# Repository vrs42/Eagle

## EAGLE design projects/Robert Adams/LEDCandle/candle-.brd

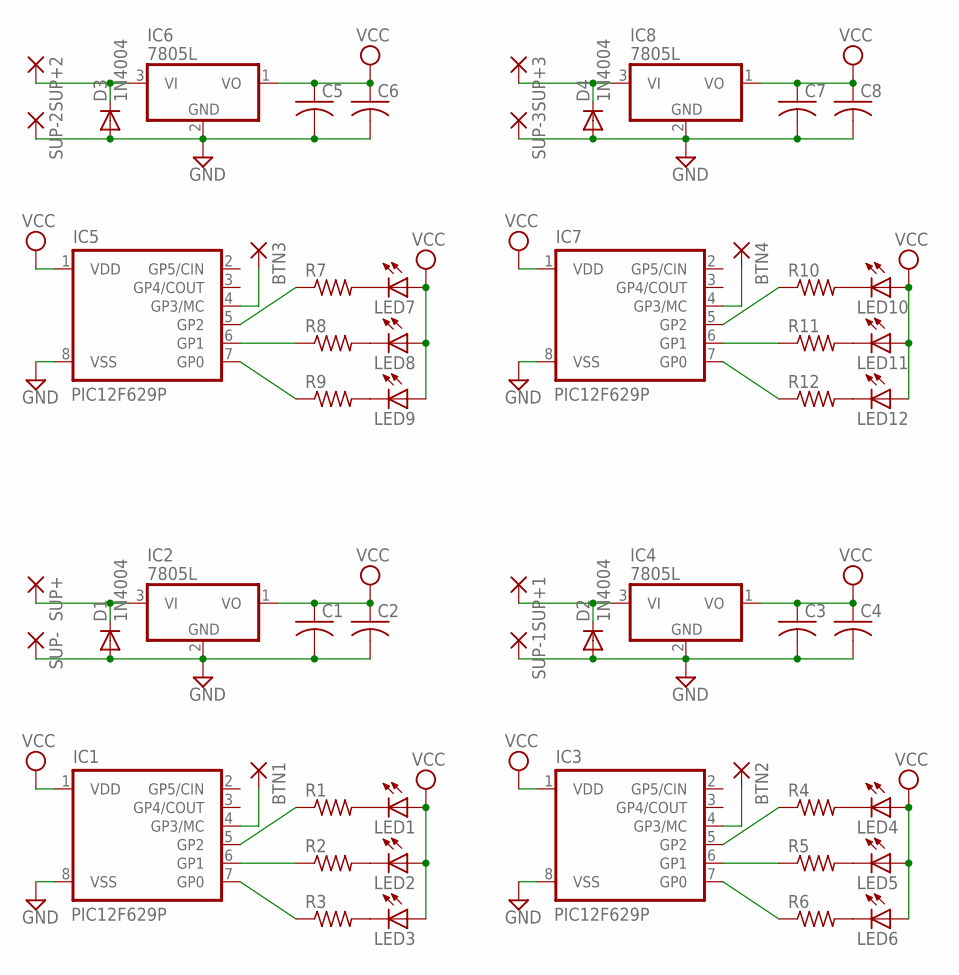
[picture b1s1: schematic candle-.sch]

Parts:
BTN1, BTN2, BTN3, BTN4: 1,6/0,8
C1, C2, C3, C4, C5, C6, C7, C8: C-US025-025X050; C025-025X050
D1, D2, D3, D4: 1N4004; DO41-10
IC1, IC3, IC5, IC7: PIC12F629P; DIL8
IC2, IC4, IC6, IC8: 7805L; TO92
LED1, LED2, LED3, LED4, LED5, LED6, LED7, LED8, LED9, LED10, LED11, LED12: LED5MM
R1, R2, R3, R4, R5, R6, R7, R8, R9, R10, R11, R12: R-US_0204/7; 0204/7
SUP+, SUP+1, SUP+2, SUP+3: 1,6/0,8
SUP-, SUP-1, SUP-2, SUP-3: 1,6/0,8

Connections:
GND: C1.2, C2.2, C3.2, C4.2, C5.2, C6.2, C7.2, C8.2, D1.A, D2.A, D3.A, D4.A, IC1.8 (VSS), IC2.2 (GND), IC3.8 (VSS), IC4.2 (GND), IC5.8 (VSS), IC6.2 (GND), IC7.8 (VSS), IC8.2 (GND), SUP-.1, SUP-1.1, SUP-2.1, SUP-3.1
unnamed: IC3.7 (GP0), R6.1
unnamed: BTN1.1, IC1.4 (GP3/MC)
unnamed: IC1.7 (GP0), R3.1
unnamed: IC1.6 (GP1), R2.1
unnamed: IC1.5 (GP2), R1.1
unnamed: LED1.K (C), R1.2
unnamed: LED2.K (C), R2.2
unnamed: LED3.K (C), R3.2
unnamed: IC3.6 (GP1), R5.1
unnamed: D1.C, IC2.3 (VI), SUP+.1
unnamed: IC3.5 (GP2), R4.1
unnamed: LED4.K (C), R4.2
unnamed: LED5.K (C), R5.2
unnamed: LED6.K (C), R6.2
unnamed: D2.C, IC4.3 (VI), SUP+1.1
unnamed: BTN2.1, IC3.4 (GP3/MC)
unnamed: IC5.7 (GP0), R9.1
unnamed: IC5.6 (GP1), R8.1
unnamed: IC5.5 (GP2), R7.1
unnamed: LED7.K (C), R7.2
unnamed: LED8.K (C), R8.2
unnamed: LED9.K (C), R9.2
unnamed: D3.C, IC6.3 (VI), SUP+2.1
unnamed: BTN3.1, IC5.4 (GP3/MC)
unnamed: IC7.7 (GP0), R12.1
unnamed: IC7.6 (GP1), R11.1
unnamed: IC7.5 (GP2), R10.1
unnamed: LED10.K (C), R10.2
unnamed: LED11.K (C), R11.2
unnamed: LED12.K (C), R12.2
unnamed: D4.C, IC8.3 (VI), SUP+3.1
unnamed: BTN4.1, IC7.4 (GP3/MC)
VCC: C1.1, C2.1, C3.1, C4.1, C5.1, C6.1, C7.1, C8.1, IC1.1 (VDD), IC2.1 (VO), IC3.1 (VDD), IC4.1 (VO), IC5.1 (VDD), IC6.1 (VO), IC7.1 (VDD), IC8.1 (VO), LED1.A, LED2.A, LED3.A, LED4.A, LED5.A, LED6.A, LED7.A, LED8.A, LED9.A, LED10.A, LED11.A, LED12.A

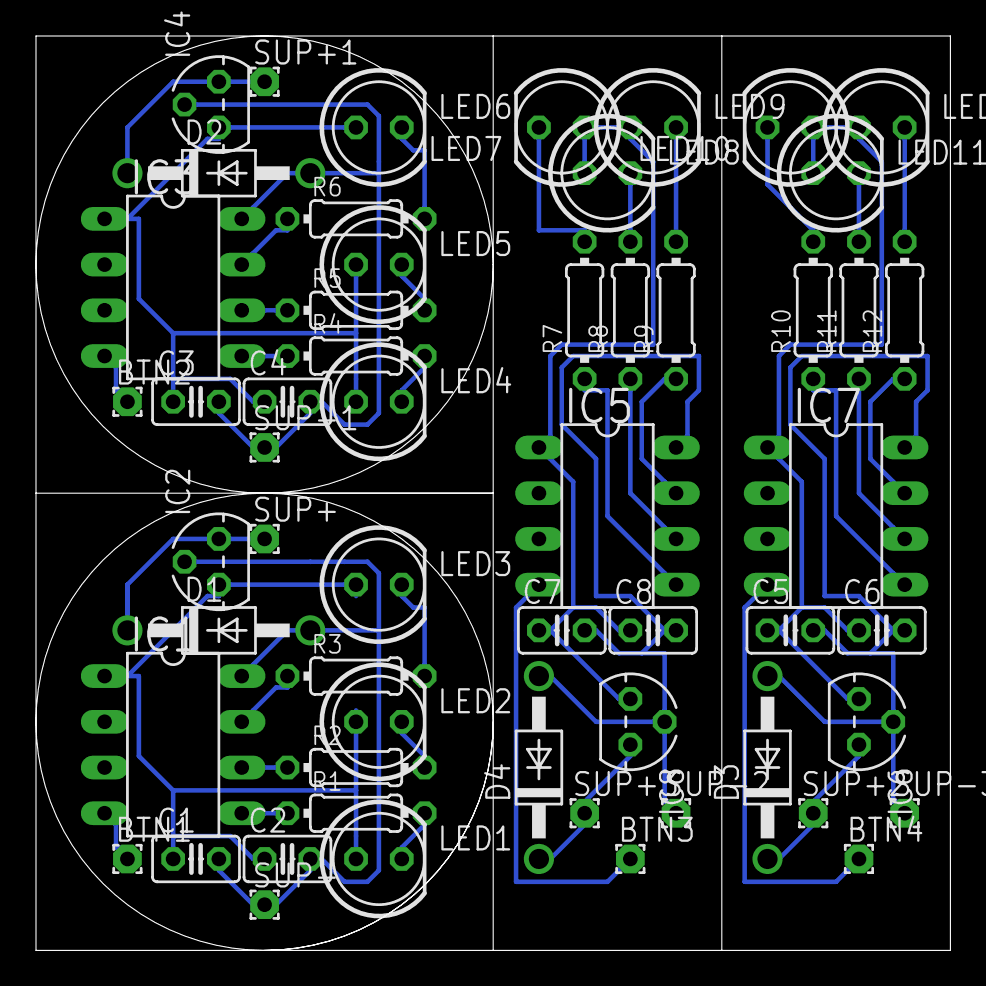
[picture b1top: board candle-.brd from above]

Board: 2 copper layers, 50.8 x 50.8 mm, 56 parts (0 on the bottom side), 34 nets.

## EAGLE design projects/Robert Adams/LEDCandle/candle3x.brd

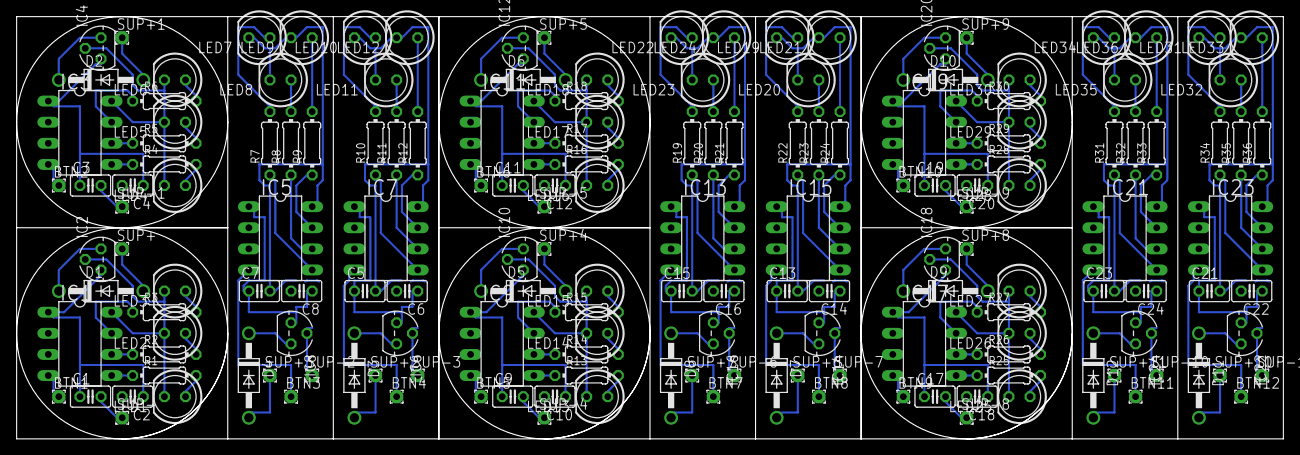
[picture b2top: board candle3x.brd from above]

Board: 2 copper layers, 152.4 x 50.8 mm, 168 parts (0 on the bottom side), 112 nets.

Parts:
BTN1, BTN2, BTN3, BTN4, BTN5, BTN6, BTN7, BTN8, BTN9, BTN10, BTN11, BTN12: 1,6/0,8
C1, C2, C3, C4, C5, C6, C7, C8, C9, C10, C11, C12, C13, C14, C15, C16, C17, C18, C19, C20, C21, C22, C23, C24: C025-025X050
D1, D2, D3, D4, D5, D6, D7, D8, D9, D10, D11, D12: 1N4004; DO41-10
IC1, IC3, IC5, IC7, IC9, IC11, IC13, IC15, IC17, IC19, IC21, IC23: PIC12F629P; DIL8
IC2, IC4, IC6, IC8, IC10, IC12, IC14, IC16, IC18, IC20, IC22, IC24: 7805L; TO92
LED1, LED2, LED3, LED4, LED5, LED6, LED7, LED8, LED9, LED10, LED11, LED12, LED13, LED14, LED15, LED16, LED17, LED18, LED19, LED20, LED21, LED22, LED23, LED24, LED25, LED26, LED27, LED28, LED29, LED30, LED31, LED32, LED33, LED34, LED35, LED36: LED5MM
R1, R2, R3, R4, R5, R6, R7, R8, R9, R10, R11, R12, R13, R14, R15, R16, R17, R18, R19, R20, R21, R22, R23, R24, R25, R26, R27, R28, R29, R30, R31, R32, R33, R34, R35, R36: 0204/7
SUP+, SUP+1, SUP+2, SUP+3, SUP+4, SUP+5, SUP+6, SUP+7, SUP+8, SUP+9, SUP+10, SUP+11: 1,6/0,8
SUP-, SUP-1, SUP-2, SUP-3, SUP-4, SUP-5, SUP-6, SUP-7, SUP-8, SUP-9, SUP-10, SUP-11: 1,6/0,8

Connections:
GND: C1.2, C2.2, C3.2, C4.2, C5.2, C6.2, C7.2, C8.2, C9.2, C10.2, C11.2, C12.2, C13.2, C14.2, C15.2, C16.2, C17.2, C18.2, C19.2, C20.2, C21.2, C22.2, C23.2, C24.2, IC1.8, IC2.2, IC3.8, IC4.2, IC5.8, IC6.2, IC7.8, IC8.2, IC9.8, IC10.2, IC11.8, IC12.2, IC13.8, IC14.2, IC15.8, IC16.2, IC17.8, IC18.2, IC19.8, IC20.2, IC21.8, IC22.2, IC23.8, IC24.2, LED1.K, LED2.K, LED3.K, LED4.K, LED5.K, LED6.K, LED7.K, LED8.K, LED9.K, LED10.K, LED11.K, LED12.K, LED13.K, LED14.K, LED15.K, LED16.K, LED17.K, LED18.K, LED19.K, LED20.K, LED21.K, LED22.K, LED23.K, LED24.K, LED25.K, LED26.K, LED27.K, LED28.K, LED29.K, LED30.K, LED31.K, LED32.K, LED33.K, LED34.K, LED35.K, LED36.K, SUP-.1, SUP-1.1, SUP-2.1, SUP-3.1, SUP-4.1, SUP-5.1, SUP-6.1, SUP-7.1, SUP-8.1, SUP-9.1, SUP-10.1, SUP-11.1
unnamed: IC3.7, R6.1
unnamed: BTN1.1, IC1.4
unnamed: IC1.7, R3.1
unnamed: IC1.6, R2.1
unnamed: IC1.5, R1.1
unnamed: LED1.A, R1.2
unnamed: LED2.A, R2.2
unnamed: LED3.A, R3.2
unnamed: IC3.6, R5.1
unnamed: D1.C, IC2.3
unnamed: IC3.5, R4.1
unnamed: LED4.A, R4.2
unnamed: LED5.A, R5.2
unnamed: LED6.A, R6.2
unnamed: D2.C, IC4.3
unnamed: BTN2.1, IC3.4
unnamed: IC5.7, R9.1
unnamed: IC5.6, R8.1
unnamed: IC5.5, R7.1
unnamed: LED7.A, R7.2
unnamed: LED8.A, R8.2
unnamed: D3.C, IC6.3
unnamed: BTN3.1, IC5.4
unnamed: IC7.7, R12.1
unnamed: IC7.6, R11.1
unnamed: IC7.5, R10.1
unnamed: LED9.A, R9.2
unnamed: LED10.A, R10.2
unnamed: LED11.A, R11.2
unnamed: D4.C, IC8.3
unnamed: BTN4.1, IC7.4
unnamed: D1.A, SUP+.1
unnamed: LED12.A, R12.2
unnamed: D3.A, SUP+2.1
unnamed: D4.A, SUP+3.1
unnamed: D2.A, SUP+1.1
unnamed: IC9.7, R15.1
unnamed: IC9.6, R14.1
unnamed: IC9.5, R13.1
unnamed: D5.C, IC10.3
unnamed: BTN5.1, IC9.4
unnamed: IC11.7, R18.1
unnamed: IC11.6, R17.1
unnamed: IC11.5, R16.1
unnamed: D6.C, IC12.3
unnamed: BTN6.1, IC11.4
unnamed: IC13.7, R21.1
unnamed: IC13.6, R20.1
unnamed: IC13.5, R19.1
unnamed: D7.C, IC14.3
unnamed: BTN7.1, IC13.4
unnamed: IC15.7, R24.1
unnamed: IC15.6, R23.1
unnamed: IC15.5, R22.1
unnamed: D8.C, IC16.3
unnamed: BTN8.1, IC15.4
unnamed: D5.A, SUP+4.1
unnamed: LED13.A, R13.2
unnamed: LED14.A, R14.2
unnamed: LED15.A, R15.2
unnamed: LED16.A, R16.2
unnamed: LED17.A, R17.2
unnamed: LED18.A, R18.2
unnamed: LED19.A, R22.2
unnamed: LED20.A, R23.2
unnamed: LED21.A, R24.2
unnamed: LED22.A, R19.2
unnamed: LED23.A, R20.2
unnamed: LED24.A, R21.2
unnamed: D7.A, SUP+6.1
unnamed: D8.A, SUP+7.1
unnamed: D6.A, SUP+5.1
unnamed: IC17.7, R27.1
unnamed: IC17.6, R26.1
unnamed: IC17.5, R25.1
unnamed: D9.C, IC18.3
unnamed: BTN9.1, IC17.4
unnamed: IC19.7, R30.1
unnamed: IC19.6, R29.1
unnamed: IC19.5, R28.1
unnamed: D10.C, IC20.3
unnamed: BTN10.1, IC19.4
unnamed: IC21.7, R33.1
unnamed: IC21.6, R32.1
unnamed: IC21.5, R31.1
unnamed: D11.C, IC22.3
unnamed: BTN11.1, IC21.4
unnamed: IC23.7, R36.1
unnamed: IC23.6, R35.1
unnamed: IC23.5, R34.1
unnamed: D12.C, IC24.3
unnamed: BTN12.1, IC23.4
unnamed: D9.A, SUP+8.1
unnamed: LED25.A, R25.2
unnamed: LED26.A, R26.2
unnamed: LED27.A, R27.2
unnamed: LED28.A, R28.2
unnamed: LED29.A, R29.2
unnamed: LED30.A, R30.2
unnamed: LED31.A, R34.2
unnamed: LED32.A, R35.2
unnamed: LED33.A, R36.2
unnamed: LED34.A, R31.2
unnamed: LED35.A, R32.2
unnamed: LED36.A, R33.2
unnamed: D11.A, SUP+10.1
unnamed: D12.A, SUP+11.1
unnamed: D10.A, SUP+9.1
VCC: C1.1, C2.1, C3.1, C4.1, C5.1, C6.1, C7.1, C8.1, IC1.1, IC2.1, IC3.1, IC4.1, IC5.1, IC6.1, IC7.1, IC8.1
VCC1: C9.1, C10.1, C11.1, C12.1, C13.1, C14.1, C15.1, C16.1, IC9.1, IC10.1, IC11.1, IC12.1, IC13.1, IC14.1, IC15.1, IC16.1
VCC2: C17.1, C18.1, C19.1, C20.1, C21.1, C22.1, C23.1, C24.1, IC17.1, IC18.1, IC19.1, IC20.1, IC21.1, IC22.1, IC23.1, IC24.1
